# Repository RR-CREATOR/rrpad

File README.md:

# rrpad
macropad

Its a 11 key macropad with a rotary encoder and an OLED Display. It uses KMK firmware

## Bill of Materials (BOM)
Qty	Name
1	Case top and bottom
11	Cherry MX switches
12	1N4148 diodes
11	Blank DSA white keycaps
1	128x32 I2C OLED screen
1	EC11 rotary encoder + knob
1	PCB
1	Seeed Studio XIAO RP2040
4	M3x16mm screws
4	M3 Heatset Inserts

## CAD:

## Schematic:

## PCB:

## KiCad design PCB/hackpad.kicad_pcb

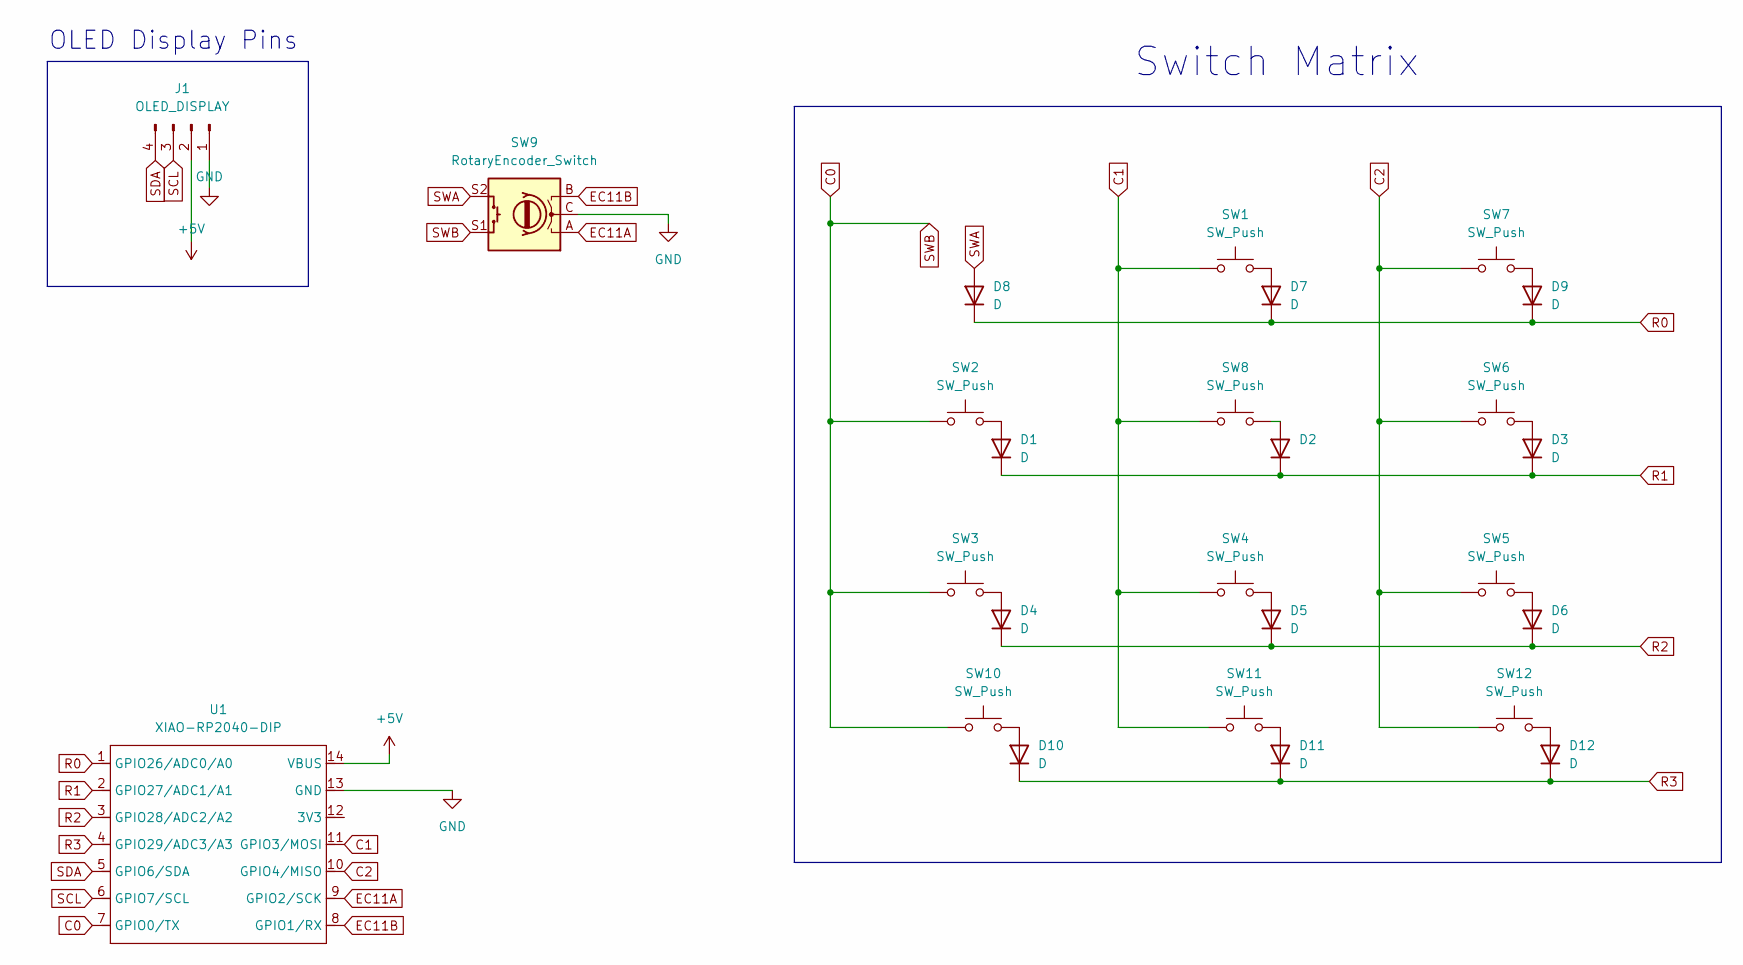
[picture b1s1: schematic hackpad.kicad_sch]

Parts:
D1, D2, D3, D4, D5, D6, D7, D8, D9, D10, D11, D12: D; D_DO-35_SOD27_P7.62mm_Horizontal
J1: OLED_DISPLAY; 0.91-OLED-4pin-128x32
SW1, SW2, SW3, SW4, SW5, SW6, SW7, SW8, SW10, SW11, SW12: SW_Push; SW_Cherry_MX_1.00u_PCB
SW9: RotaryEncoder_Switch; RotaryEncoder_Alps_EC11E-Switch_Vertical_H20mm
U1: XIAO-RP2040-DIP

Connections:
+5V: J1.2, U1.14 (VBUS)
C0: SW2.1, SW3.1, SW9.S1, SW10.1, U1.7 (GPIO0/TX)
C1: SW1.1, SW4.1, SW8.1, SW11.1, U1.11 (GPIO3/MOSI)
C2: SW5.1, SW6.1, SW7.1, SW12.1, U1.10 (GPIO4/MISO)
EC11A: SW9.A, U1.9 (GPIO2/SCK)
EC11B: SW9.B, U1.8 (GPIO1/RX)
GND: J1.1, SW9.C, U1.13 (GND)
unnamed: D1.2 (A), SW2.2
unnamed: D2.2 (A), SW8.2
unnamed: D3.2 (A), SW6.2
unnamed: D4.2 (A), SW3.2
unnamed: D5.2 (A), SW4.2
unnamed: D6.2 (A), SW5.2
unnamed: D7.2 (A), SW1.2
unnamed: D9.2 (A), SW7.2
unnamed: D10.2 (A), SW10.2
unnamed: D11.2 (A), SW11.2
unnamed: D12.2 (A), SW12.2
R0: D7.1 (K), D8.1 (K), D9.1 (K), U1.1 (GPIO26/ADC0/A0)
R1: D1.1 (K), D2.1 (K), D3.1 (K), U1.2 (GPIO27/ADC1/A1)
R2: D4.1 (K), D5.1 (K), D6.1 (K), U1.3 (GPIO28/ADC2/A2)
R3: D10.1 (K), D11.1 (K), D12.1 (K), U1.4 (GPIO29/ADC3/A3)
SCL: J1.3, U1.6 (GPIO7/SCL)
SDA: J1.4, U1.5 (GPIO6/SDA)
SWA: D8.2 (A), SW9.S2

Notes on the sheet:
Switch Matrix
OLED Display Pins

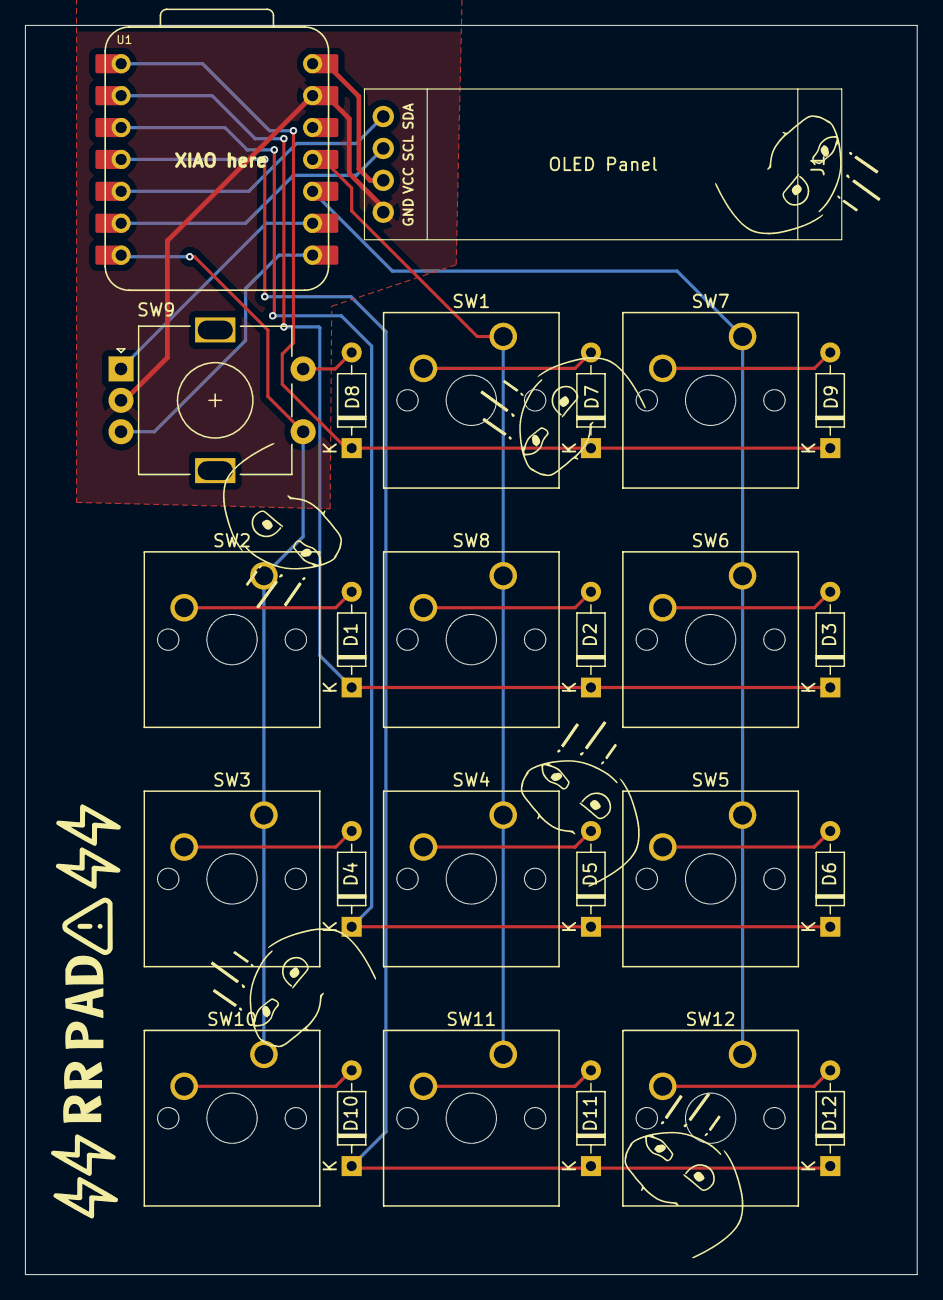
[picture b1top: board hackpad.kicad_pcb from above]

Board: 2 copper layers, 71.0 x 99.4 mm, 26 parts (0 on the bottom side), 25 nets.

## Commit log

2025-07-21 Adding files
    added all files
2026-06-27 Map rrpad copy paste keys
2026-06-27 Fix encoder toggle for current KMK
2026-06-27 Align firmware with rrpad PCB matrix
2026-06-27 Improve rrpad encoder and display
